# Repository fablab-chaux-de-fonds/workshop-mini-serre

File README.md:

# workshop-mini-serre
Atelier pour la réalisation d'une mini serre domotisée

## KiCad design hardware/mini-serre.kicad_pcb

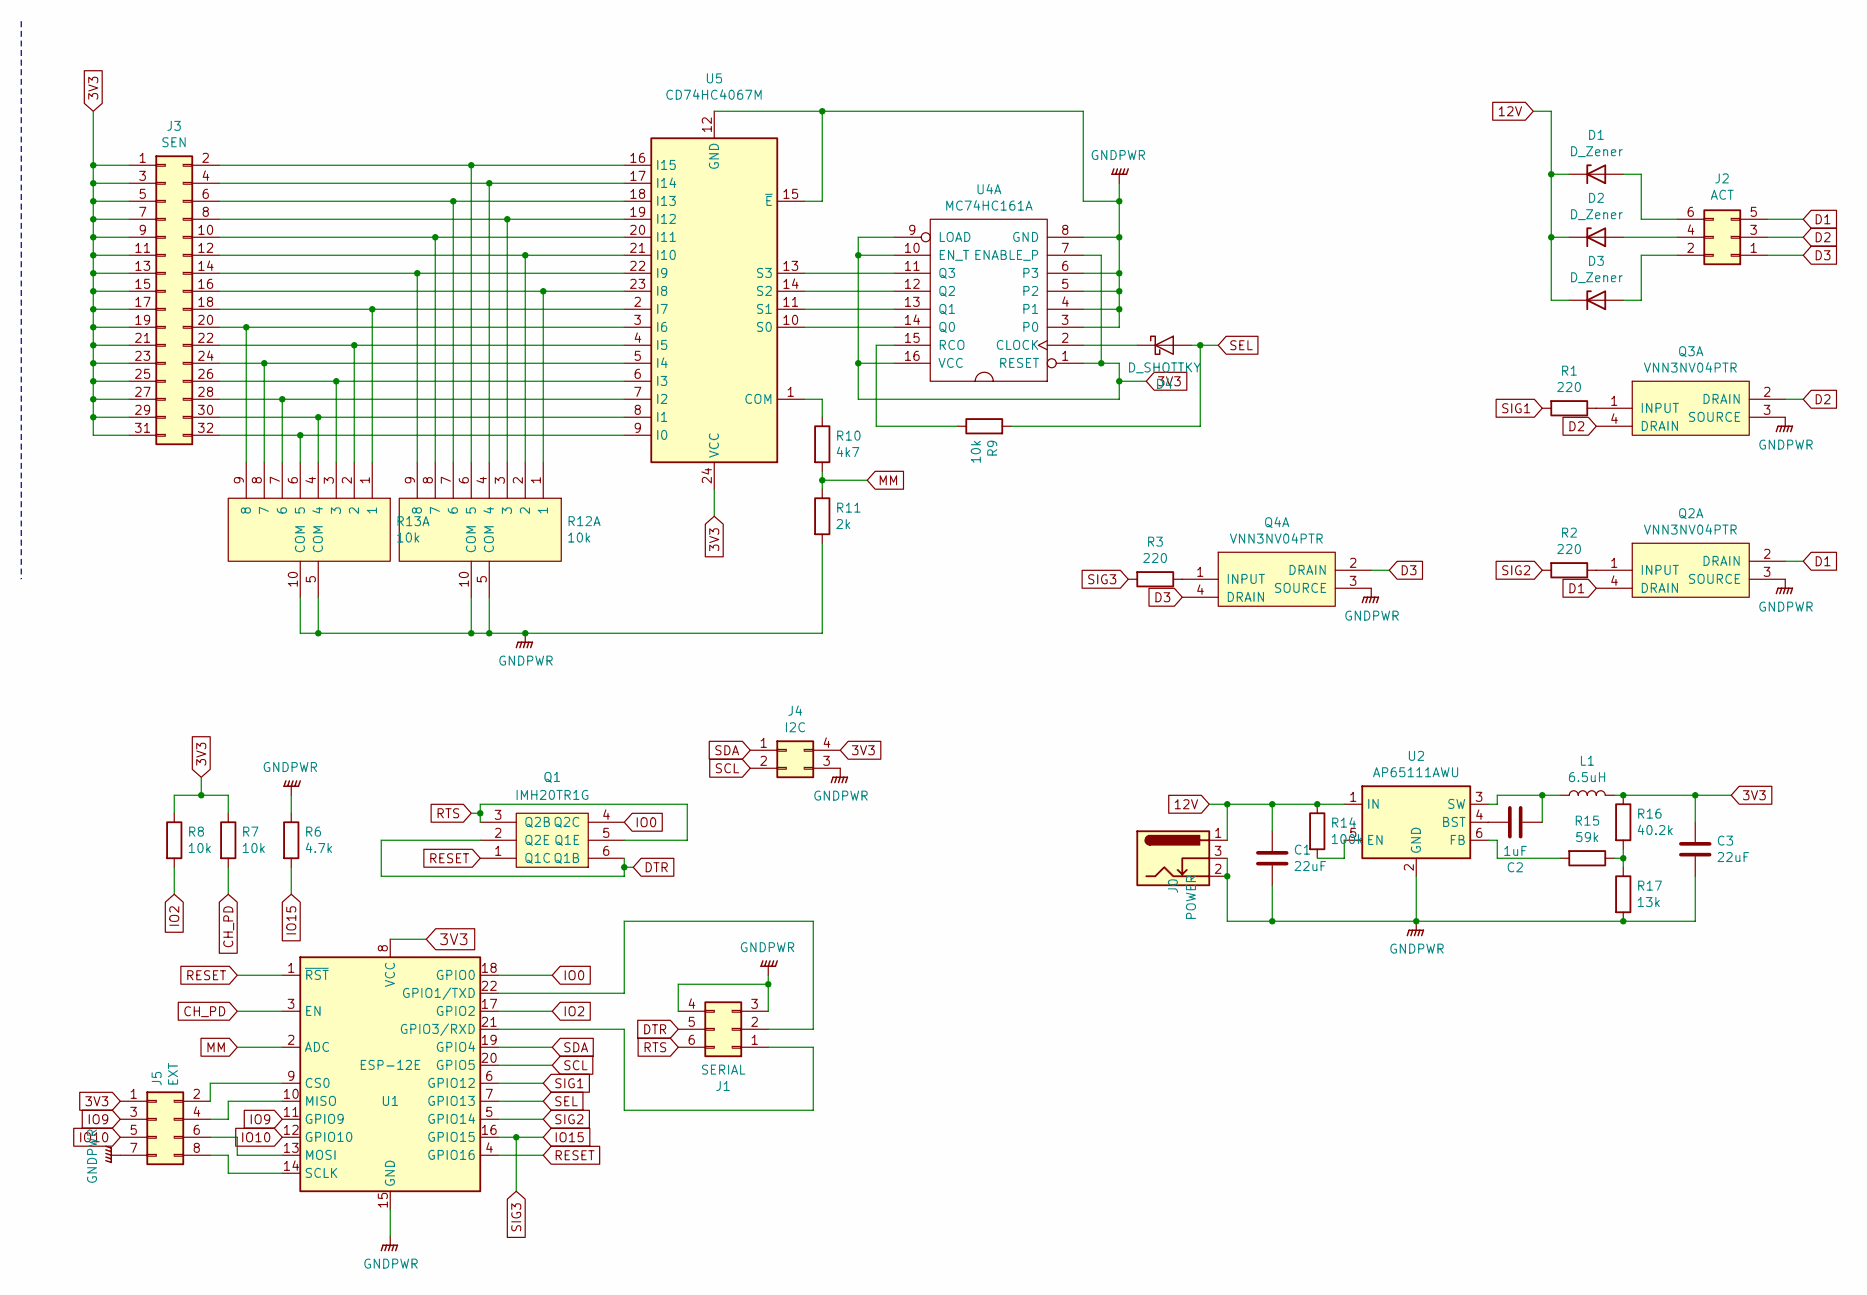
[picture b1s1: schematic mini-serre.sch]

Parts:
C1, C3: 22uF; C_1206_3216Metric_Pad1.42x1.75mm_HandSolder
C2: 1uF; C_1206_3216Metric_Pad1.42x1.75mm_HandSolder
D1, D2, D3: D_Zener; D_SMA_Handsoldering; Mouser 78-BZG05C5V6-M3-08
D4: D_SHOTTKY; D_SOD-123
J0: POWER; BarrelJack_Wuerth_6941xx301002
J1: SERIAL; PinHeader_2x03_P2.54mm_Vertical_SMD
J2: ACT; PinHeader_2x03_P2.54mm_Vertical_SMD
J3: SEN; PinHeader_2x16_P2.54mm_Vertical_SMD
J4: I2C; PinHeader_2x02_P2.54mm_Vertical_SMD
J5: EXT; PinHeader_2x04_P2.54mm_Vertical_SMD
L1: 6.5uH; L_Taiyo-Yuden_NR-10050_9.8x10.0mm_HandSoldering; Mouser 963-NR10050T6R5N
Q1: IMH20TR1G; SC-74-6_1.5x2.9mm_P0.95mm
Q2, Q3, Q4: VNN3NV04PTR; SOT-223
R1, R2, R3: 220; R_1210_3225Metric_Pad1.42x2.65mm_HandSolder
R6: 4.7k; R_1210_3225Metric_Pad1.42x2.65mm_HandSolder
R7, R8, R9: 10k; R_1210_3225Metric_Pad1.42x2.65mm_HandSolder
R10: 4k7; R_1210_3225Metric_Pad1.42x2.65mm_HandSolder
R11: 2k; R_1210_3225Metric_Pad1.42x2.65mm_HandSolder
R12, R13: 10k; R_Array_Convex_5x1206
R14: 100k; R_1206_3216Metric_Pad1.42x1.75mm_HandSolder; Mouser 71-CRCW1206100KFKEAC
R15: 59k; R_1206_3216Metric_Pad1.42x1.75mm_HandSolder; Mouser 667-ERJ-8ENF5902V
R16: 40.2k; R_1206_3216Metric_Pad1.42x1.75mm_HandSolder; Mouser 652-CR1206FX-4022ELF
R17: 13k; R_1206_3216Metric_Pad1.42x1.75mm_HandSolder; Mouser 667-ERJ-8ENF1302V
U1: ESP-12E
U2: AP65111AWU; TSOT-23-6
U4: MC74HC161A; SOIC-16_4.55x10.3mm_P1.27mm
U5: CD74HC4067M; SOIC-24W_7.5x15.4mm_P1.27mm

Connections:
3V3: C3.1, J3.1, J3.3, J3.5, J3.7, J3.9, J3.11, J3.13, J3.15, J3.17, J3.19, J3.21, J3.23, J3.25, J3.27, J3.29, J3.31, J4.4, J5.1, L1.2, R7.1, R8.1, R16.1, U1.8 (VCC), U4.1 (RESET), U4.7 (ENABLE_P), U4.9 (LOAD), U4.10 (EN_T), U4.16 (VCC), U5.24 (VCC)
12V: C1.1, D1.1 (K), D2.1 (K), D3.1 (K), J0.1, R14.1, U2.1 (IN)
CH_PD: R7.2, U1.3 (EN)
D1: J2.5, Q2.2 (DRAIN), Q2.4 (DRAIN)
D2: J2.3, Q3.2 (DRAIN), Q3.4 (DRAIN)
D3: J2.1, Q4.2 (DRAIN), Q4.4 (DRAIN)
DTR: J1.5, Q1.2 (Q2E), Q1.6 (Q1B)
GNDPWR: C1.2, C3.2, J0.2, J0.3, J1.3, J1.4, J4.3, J5.7, Q2.3 (SOURCE), Q3.3 (SOURCE), Q4.3 (SOURCE), R6.1, R11.2, R12.5 (COM), R12.10 (COM), R13.5 (COM), R13.10 (COM), R17.2, U1.15 (GND), U2.2 (GND), U4.3 (P0), U4.4 (P1), U4.5 (P2), U4.6 (P3), U4.8 (GND), U5.12 (GND), U5.15 (~E)
IO0: Q1.4 (Q2C), U1.18 (GPIO0)
IO2: R8.2, U1.17 (GPIO2)
IO9: J5.3, U1.11 (GPIO9)
IO10: J5.5, U1.12 (GPIO10)
IO15: R3.2, R6.2, U1.16 (GPIO15)
MM: R10.2, R11.1, U1.2 (ADC)
unnamed: C2.1, L1.1, U2.3 (SW)
unnamed: C2.2, U2.4 (BST)
unnamed: D1.2 (A), J2.6
unnamed: D2.2 (A), J2.4
unnamed: D3.2 (A), J2.2
unnamed: D4.1 (K), U4.2 (CLOCK)
unnamed: J1.1, U1.21 (GPIO3/RXD)
unnamed: J1.2, U1.22 (GPIO1/TXD)
unnamed: J3.2, R12.6 (5), U5.16 (I15)
unnamed: J3.4, R12.4, U5.17 (I14)
unnamed: J3.6, R12.7 (6), U5.18 (I13)
unnamed: J3.8, R12.3, U5.19 (I12)
unnamed: J3.10, R12.8 (7), U5.20 (I11)
unnamed: J3.12, R12.2, U5.21 (I10)
unnamed: J3.14, R12.9 (8), U5.22 (I9)
unnamed: J3.16, R12.1, U5.23 (I8)
unnamed: J3.18, R13.1, U5.2 (I7)
unnamed: J3.20, R13.9 (8), U5.3 (I6)
unnamed: J3.22, R13.2, U5.4 (I5)
unnamed: J3.24, R13.8 (7), U5.5 (I4)
unnamed: J3.26, R13.3, U5.6 (I3)
unnamed: J3.28, R13.7 (6), U5.7 (I2)
unnamed: J3.30, R13.4, U5.8 (I1)
unnamed: J3.32, R13.6 (5), U5.9 (I0)
unnamed: J5.2, U1.9 (CS0)
unnamed: J5.4, U1.10 (MISO)
unnamed: J5.6, U1.13 (MOSI)
unnamed: J5.8, U1.14 (SCLK)
unnamed: Q2.1 (INPUT), R2.1
unnamed: Q3.1 (INPUT), R1.1
unnamed: Q4.1 (INPUT), R3.1
unnamed: R9.1, U4.15 (RCO)
unnamed: R10.1, U5.1 (COM)
unnamed: R14.2, U2.5 (EN)
unnamed: R15.1, R16.2, R17.1
unnamed: R15.2, U2.6 (FB)
unnamed: U4.11 (Q3), U5.13 (S3)
unnamed: U4.12 (Q2), U5.14 (S2)
unnamed: U4.13 (Q1), U5.11 (S1)
unnamed: U4.14 (Q0), U5.10 (S0)
RESET: Q1.1 (Q1C), U1.1 (~RST), U1.4 (GPIO16)
RTS: J1.6, Q1.3 (Q2B), Q1.5 (Q1E)
SCL: J4.2, U1.20 (GPIO5)
SDA: J4.1, U1.19 (GPIO4)
SEL: D4.2 (A), R9.2, U1.7 (GPIO13)
SIG1: R1.2, U1.6 (GPIO12)
SIG2: R2.2, U1.5 (GPIO14)

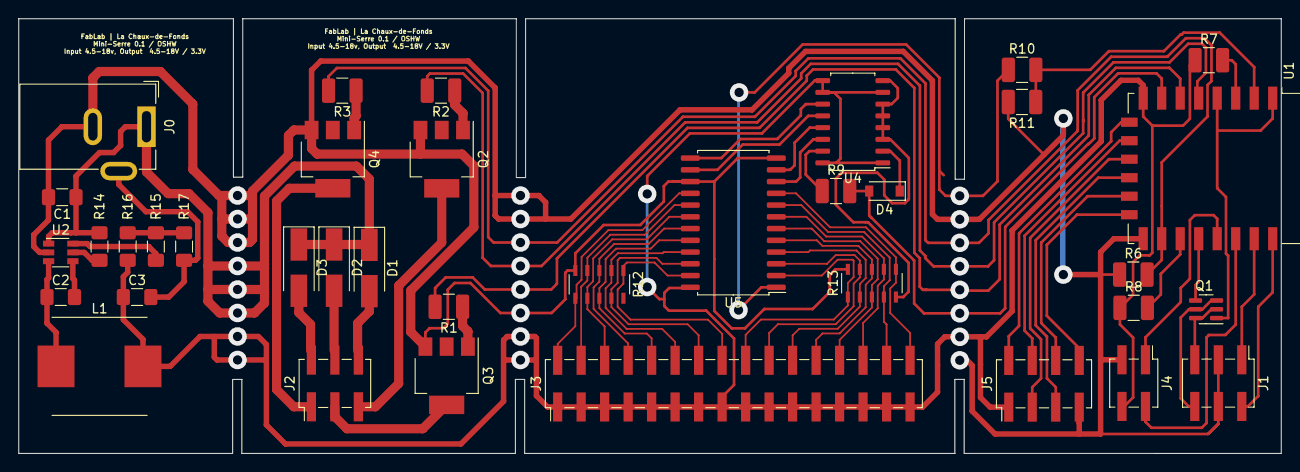
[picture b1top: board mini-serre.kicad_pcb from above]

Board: 2 copper layers, 136.5 x 47.0 mm, 37 parts (0 on the bottom side), 61 nets.

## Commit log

2020-05-23 initial commit work in progress
2020-05-24 update schematics with buck converter, add part info and begin routing
2020-05-30 backup before ground and power plane attempt
2020-06-01 splitted in 3 modules : power in, power outputs, analog multiplexer, logic
2021-03-18 Current state
2021-03-19 Use INI file for library dependencies
2021-03-19 FIX build issues
